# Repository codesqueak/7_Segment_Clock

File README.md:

# 7 Segment 24 Hour LED Clock

A pure logic, 7 segment 24 hour clock using large 7 segment displays

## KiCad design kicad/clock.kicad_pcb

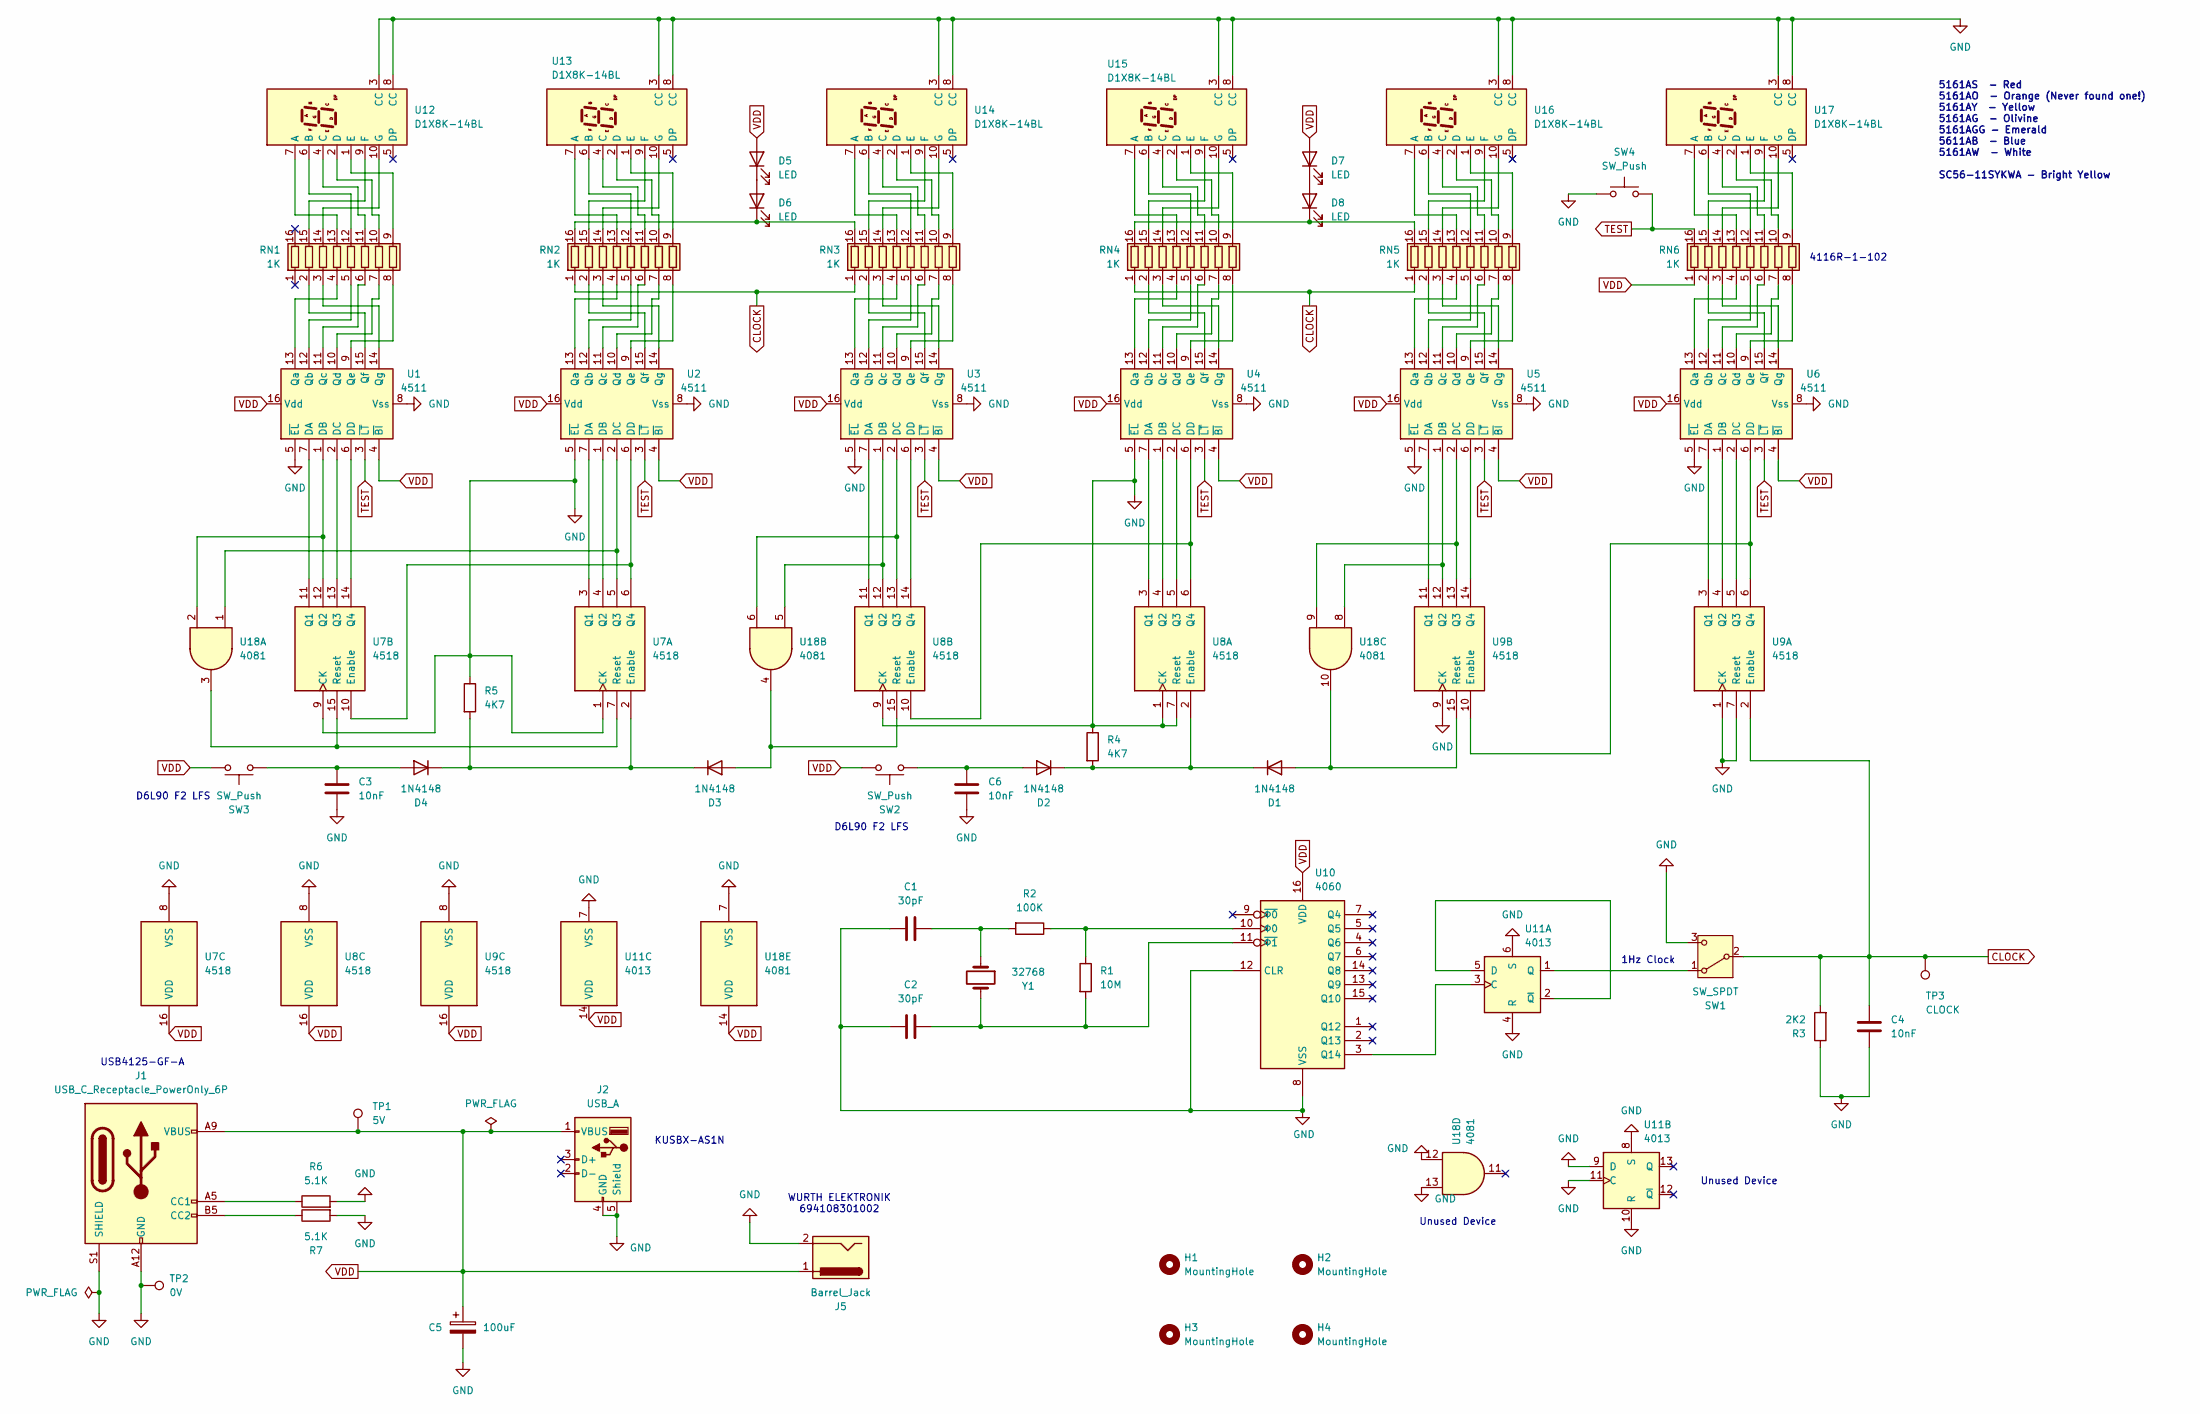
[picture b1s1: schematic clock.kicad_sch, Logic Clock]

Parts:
C1, C2: 30pF; C_Disc_D6.0mm_W2.5mm_P5.00mm
C3, C4, C6: 10nF; C_Disc_D6.0mm_W2.5mm_P5.00mm
C5: 100uF; CP_Radial_D5.0mm_P2.50mm
D1, D2, D3, D4: 1N4148; D_DO-35_SOD27_P7.62mm_Horizontal
D5, D6, D7, D8: LED; LED_D3.0mm
H1, H2, H3, H4: MountingHole; MountingHole_3.5mm
J1: USB_C_Receptacle_PowerOnly_6P; USB_C_Receptacle_GCT_USB4125-xx-x-0190_6P_TopMnt_Horizontal
J2: USB_A; USB_A_Kycon_KUSBX-AS1N-B_Horizontal
J5: Barrel_Jack; BarrelJack_Wuerth_6941xx301002
R1: 10M; R_Axial_DIN0309_L9.0mm_D3.2mm_P12.70mm_Horizontal
R2: 100K; R_Axial_DIN0309_L9.0mm_D3.2mm_P12.70mm_Horizontal
R3: 2K2; R_Axial_DIN0309_L9.0mm_D3.2mm_P12.70mm_Horizontal
R4, R5: 4K7; R_Axial_DIN0309_L9.0mm_D3.2mm_P12.70mm_Horizontal
R6, R7: 5.1K; R_Axial_DIN0309_L9.0mm_D3.2mm_P12.70mm_Horizontal
RN1, RN2, RN3, RN4, RN5, RN6: 1K; DIP-16_W7.62mm_Socket
SW1: SW_SPDT; SW_Slide-03_Pin-2-Common_10x2.5x6.4_P2.54mm
SW2, SW3, SW4: SW_Push; SW_PUSH_6mm_H5mm
TP1: 5V; TestPoint_THTPad_2.0x2.0mm_Drill1.0mm
TP2: 0V; TestPoint_THTPad_2.0x2.0mm_Drill1.0mm
TP3: CLOCK; TestPoint_THTPad_2.0x2.0mm_Drill1.0mm
U1, U2, U3, U4, U5, U6: 4511; DIP-16_W7.62mm_Socket
U7, U8, U9: 4518; DIP-16_W7.62mm_Socket
U10: 4060; DIP-16_W7.62mm_Socket
U11: 4013; DIP-14_W7.62mm_Socket
U12, U13, U14, U15, U16, U17: D1X8K-14BL; D1X8K
U18: 4081; DIP-14_W7.62mm_Socket
Y1: 32768; Crystal_AT310_D3.0mm_L10.0mm_Horizontal

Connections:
CLOCK: C4.1, R3.2, RN2.1 (R1.1), RN3.1 (R1.1), RN4.1 (R1.1), RN5.1 (R1.1), SW1.2 (B), TP3.1, U9.2 (Enable)
GND: C1.1, C2.1, C3.2, C4.2, C5.2, C6.2, J1.A12 (GND), J1.B12 (GND), J1.S1 (SHIELD), J2.4 (GND), J2.5 (Shield), J5.2, R3.1, R4.1, R5.1, R6.2, R7.2, SW1.3 (C), SW4.2, TP2.1, U1.5 (~EL), U1.8 (Vss), U2.5 (~EL), U2.8 (Vss), U3.5 (~EL), U3.8 (Vss), U4.5 (~EL), U4.8 (Vss), U5.5 (~EL), U5.8 (Vss), U6.5 (~EL), U6.8 (Vss), U7.1 (CK), U7.8 (VSS), U7.9 (CK), U8.1 (CK), U8.7 (Reset), U8.8 (VSS), U8.9 (CK), U9.1 (CK), U9.7 (Reset), U9.8 (VSS), U9.9 (CK), U10.8 (VSS), U10.12 (CLR), U11.4 (R), U11.6 (S), U11.7 (VSS), U11.8 (S), U11.9 (D), U11.10 (R), U11.11 (C), U12.3 (CC), U12.8 (CC), U13.3 (CC), U13.8 (CC), U14.3 (CC), U14.8 (CC), U15.3 (CC), U15.8 (CC), U16.3 (CC), U16.8 (CC), U17.3 (CC), U17.8 (CC), U18.7 (VSS), U18.12, U18.13
unnamed: C1.2, R2.2, Y1.1
unnamed: D1.2 (A), U9.15 (Reset), U18.10
unnamed: D1.1 (K), D2.1 (K), R4.2, U8.2 (Enable)
unnamed: C6.1, D2.2 (A), SW2.2
unnamed: D3.2 (A), U8.15 (Reset), U18.4
unnamed: D3.1 (K), D4.1 (K), R5.2, U7.2 (Enable)
unnamed: C3.1, D4.2 (A), SW3.2
unnamed: D5.1 (K), D6.2 (A)
unnamed: D6.1 (K), RN2.16 (R1.2), RN3.16 (R1.2)
unnamed: D7.1 (K), D8.2 (A)
unnamed: D8.1 (K), RN4.16 (R1.2), RN5.16 (R1.2)
unnamed: J1.A5 (CC1), R6.1
unnamed: J1.B5 (CC2), R7.1
unnamed: RN1.2 (R2.1), U1.15 (Qf)
unnamed: RN1.15 (R2.2), U12.9 (F)
unnamed: RN1.3 (R3.1), U1.14 (Qg)
unnamed: RN1.14 (R3.2), U12.10 (G)
unnamed: RN1.4 (R4.1), U1.13 (Qa)
unnamed: RN1.13 (R4.2), U12.7 (A)
unnamed: RN1.5 (R5.1), U1.12 (Qb)
unnamed: RN1.12 (R5.2), U12.6 (B)
unnamed: RN1.6 (R6.1), U1.11 (Qc)
unnamed: RN1.11 (R6.2), U12.4 (C)
unnamed: RN1.7 (R7.1), U1.10 (Qd)
unnamed: RN1.10 (R7.2), U12.2 (D)
unnamed: RN1.8 (R8.1), U1.9 (Qe)
unnamed: RN1.9 (R8.2), U12.1 (E)
unnamed: RN2.2 (R2.1), U2.15 (Qf)
unnamed: RN2.15 (R2.2), U13.9 (F)
unnamed: RN2.3 (R3.1), U2.14 (Qg)
unnamed: RN2.14 (R3.2), U13.10 (G)
unnamed: RN2.4 (R4.1), U2.13 (Qa)
unnamed: RN2.13 (R4.2), U13.7 (A)
unnamed: RN2.5 (R5.1), U2.12 (Qb)
unnamed: RN2.12 (R5.2), U13.6 (B)
unnamed: RN2.6 (R6.1), U2.11 (Qc)
unnamed: RN2.11 (R6.2), U13.4 (C)
unnamed: RN2.7 (R7.1), U2.10 (Qd)
unnamed: RN2.10 (R7.2), U13.2 (D)
unnamed: RN2.8 (R8.1), U2.9 (Qe)
unnamed: RN2.9 (R8.2), U13.1 (E)
unnamed: RN3.2 (R2.1), U3.15 (Qf)
unnamed: RN3.15 (R2.2), U14.9 (F)
unnamed: RN3.3 (R3.1), U3.14 (Qg)
unnamed: RN3.14 (R3.2), U14.10 (G)
unnamed: RN3.4 (R4.1), U3.13 (Qa)
unnamed: RN3.13 (R4.2), U14.7 (A)
unnamed: RN3.5 (R5.1), U3.12 (Qb)
unnamed: RN3.12 (R5.2), U14.6 (B)
unnamed: RN3.6 (R6.1), U3.11 (Qc)
unnamed: RN3.11 (R6.2), U14.4 (C)
unnamed: RN3.7 (R7.1), U3.10 (Qd)
unnamed: RN3.10 (R7.2), U14.2 (D)
unnamed: RN3.8 (R8.1), U3.9 (Qe)
unnamed: RN3.9 (R8.2), U14.1 (E)
unnamed: RN4.2 (R2.1), U4.15 (Qf)
unnamed: RN4.15 (R2.2), U15.9 (F)
unnamed: RN4.3 (R3.1), U4.14 (Qg)
unnamed: RN4.14 (R3.2), U15.10 (G)
unnamed: RN4.4 (R4.1), U4.13 (Qa)
unnamed: RN4.13 (R4.2), U15.7 (A)
unnamed: RN4.5 (R5.1), U4.12 (Qb)
unnamed: RN4.12 (R5.2), U15.6 (B)
unnamed: RN4.6 (R6.1), U4.11 (Qc)
unnamed: RN4.11 (R6.2), U15.4 (C)
unnamed: RN4.7 (R7.1), U4.10 (Qd)
unnamed: RN4.10 (R7.2), U15.2 (D)
unnamed: RN4.8 (R8.1), U4.9 (Qe)
unnamed: RN4.9 (R8.2), U15.1 (E)
unnamed: RN5.2 (R2.1), U5.15 (Qf)
unnamed: RN5.15 (R2.2), U16.9 (F)
unnamed: RN5.3 (R3.1), U5.14 (Qg)
unnamed: RN5.14 (R3.2), U16.10 (G)
unnamed: RN5.4 (R4.1), U5.13 (Qa)
unnamed: RN5.13 (R4.2), U16.7 (A)
unnamed: RN5.5 (R5.1), U5.12 (Qb)
unnamed: RN5.12 (R5.2), U16.6 (B)
unnamed: RN5.6 (R6.1), U5.11 (Qc)
unnamed: RN5.11 (R6.2), U16.4 (C)
unnamed: RN5.7 (R7.1), U5.10 (Qd)
unnamed: RN5.10 (R7.2), U16.2 (D)
unnamed: RN5.8 (R8.1), U5.9 (Qe)
unnamed: RN5.9 (R8.2), U16.1 (E)
unnamed: RN6.2 (R2.1), U6.15 (Qf)
unnamed: RN6.15 (R2.2), U17.9 (F)
unnamed: RN6.3 (R3.1), U6.14 (Qg)
unnamed: RN6.14 (R3.2), U17.10 (G)
unnamed: RN6.4 (R4.1), U6.13 (Qa)
unnamed: RN6.13 (R4.2), U17.7 (A)
unnamed: RN6.5 (R5.1), U6.12 (Qb)
unnamed: RN6.12 (R5.2), U17.6 (B)
unnamed: RN6.6 (R6.1), U6.11 (Qc)
unnamed: RN6.11 (R6.2), U17.4 (C)
unnamed: RN6.7 (R7.1), U6.10 (Qd)
unnamed: RN6.10 (R7.2), U17.2 (D)
unnamed: RN6.8 (R8.1), U6.9 (Qe)
unnamed: RN6.9 (R8.2), U17.1 (E)
unnamed: SW1.1 (A), U11.1 (Q)
unnamed: U1.7 (DA), U7.11 (Q1)
unnamed: U1.1 (DB), U7.12 (Q2), U18.2
unnamed: U1.2 (DC), U7.13 (Q3)
unnamed: U1.6 (DD), U7.14 (Q4)
unnamed: U2.7 (DA), U7.3 (Q1)
unnamed: U2.1 (DB), U7.4 (Q2)
unnamed: U2.2 (DC), U7.5 (Q3), U18.1
unnamed: U2.6 (DD), U7.6 (Q4), U7.10 (Enable)
unnamed: U3.7 (DA), U8.11 (Q1)
unnamed: U3.1 (DB), U8.12 (Q2), U18.5
unnamed: U3.2 (DC), U8.13 (Q3), U18.6
unnamed: U3.6 (DD), U8.14 (Q4)
unnamed: U4.7 (DA), U8.3 (Q1)
unnamed: U4.1 (DB), U8.4 (Q2)
unnamed: U4.2 (DC), U8.5 (Q3)
unnamed: U4.6 (DD), U8.6 (Q4), U8.10 (Enable)
unnamed: U5.7 (DA), U9.11 (Q1)
unnamed: U5.1 (DB), U9.12 (Q2), U18.8
unnamed: U5.2 (DC), U9.13 (Q3), U18.9
unnamed: U5.6 (DD), U9.14 (Q4)
unnamed: U6.7 (DA), U9.3 (Q1)
unnamed: U6.1 (DB), U9.4 (Q2)
unnamed: U6.2 (DC), U9.5 (Q3)
unnamed: U6.6 (DD), U9.6 (Q4), U9.10 (Enable)
unnamed: U7.7 (Reset), U7.15 (Reset), U18.3
unnamed: U10.3 (Q14), U11.3 (C)
unnamed: C2.2, R1.2, U10.11 (~Φ1), Y1.2
unnamed: R1.1, R2.1, U10.10 (Φ0)
unnamed: U11.2 (~Q), U11.5 (D)
TEST: RN6.16 (R1.2), SW4.1, U1.3 (~LT), U2.3 (~LT), U3.3 (~LT), U4.3 (~LT), U5.3 (~LT), U6.3 (~LT)
VDD: C5.1, D5.2 (A), D7.2 (A), J1.A9 (VBUS), J1.B9 (VBUS), J2.1 (VBUS), J5.1, RN6.1 (R1.1), SW2.1, SW3.1, TP1.1, U1.4 (~BI), U1.16 (Vdd), U2.4 (~BI), U2.16 (Vdd), U3.4 (~BI), U3.16 (Vdd), U4.4 (~BI), U4.16 (Vdd), U5.4 (~BI), U5.16 (Vdd), U6.4 (~BI), U6.16 (Vdd), U7.16 (VDD), U8.16 (VDD), U9.16 (VDD), U10.16 (VDD), U11.14 (VDD), U18.14 (VDD)

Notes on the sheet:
Unused Device
USB4125-GF-A
5161AS - Red 5161AO - Orange (Never found one!) 5161AY - Yellow 5161AG - Olivine 5161AGG - Emerald 5611AB - Blue 5161AW - White SC56-11SYKWA - Bright Yellow
D6L90 F2 LFS
WURTH ELEKTRONIK 694108301002
4116R-1-102
1Hz Clock
KUSBX-AS1N

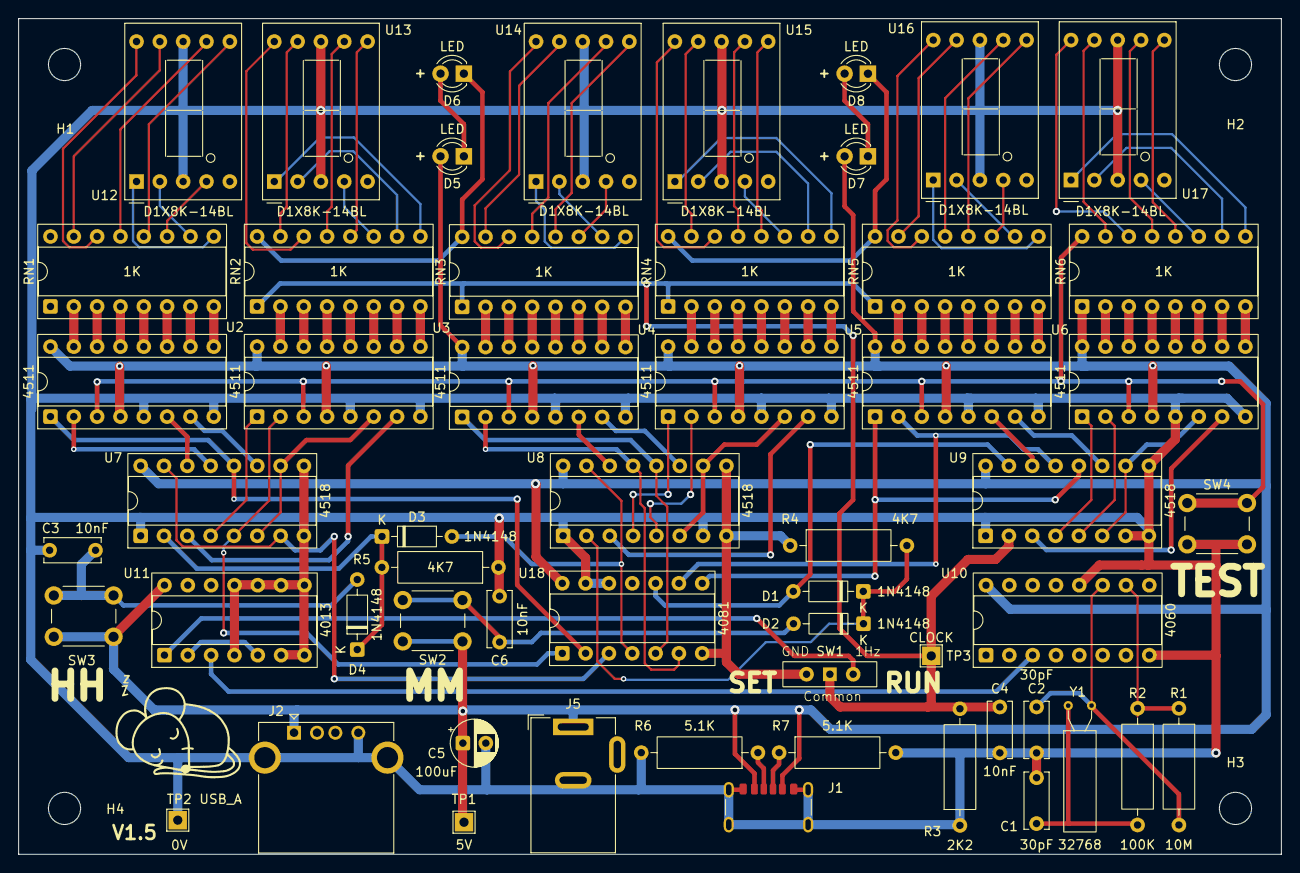
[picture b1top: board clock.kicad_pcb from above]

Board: 2 copper layers, 137.5 x 91.0 mm, 62 parts (1 on the bottom side), 131 nets.

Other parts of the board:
G001: LOGO; sleepymouse_very_small
G001#2: LOGO; qr-code

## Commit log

2025-11-17 Fist upload
2025-11-17 Update README.md
    Bad format
2025-11-17 Add qr code etc
2025-12-17 Update docs
2026-01-08 Documentation
